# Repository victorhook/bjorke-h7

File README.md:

# 🛩️ Bjorke H7 Flight Controller

Bjorke H7 is a fully open source high-performance, ArduPilot-compatible flight controller built around the powerful STM32H743VIT6 MCU. Designed for flexibility and reliability, it supports a wide range of applications—from autonomous drones to experimental robotics.

---

## 🔧 Key Features

### ⚙️ Processing Power
- **MCU**: STM32H743VIT6 (480 MHz, 2MB Flash, 1MB RAM)

### 🧭 Sensors
- **IMU**: ICM-42688-P – ultra-low noise 6-axis motion tracking
- **Barometer**: BMP388 – high-accuracy altimeter for reliable altitude estimation

### 🔄 Interfaces & I/O
- **8x Motor Outputs** via 2x ESC 8-pin JST connectors
- **8x UARTs** for telemetry, GPS, companion computers, etc.
- **1x I²C** for external sensors or peripherals
- **3x Servo Outputs** + **1x dedicated GPIO**
- **1x RGB Status LED**
- **2x extra ADC Input Pins** for external sensors
- **1x CAN** (with onboard TJA1051TK/3 transceiver) – plug-and-play UAVCAN support

### 💾 Storage & Logging
- **MicroSD card slot** for robust onboard logging

### 🔌 Power Architecture
- **5V @ 3A** DC-DC
- **3.3V @ 3A** DC-DC

---

## ⚡ Designed for ArduPilot
Bjorke H7 runs **ArduPilot firmware** with support for:
- Real-time telemetry
- In-flight parameter updates
- MAVLink compatibility
- Full hardware-in-the-loop (HITL) testing
- CAN-based peripherals (UAVCAN GPS, ESCs, etc.)

---

## 🚧 Status
- [X] PCB rev.A designed and ordered
- [X] hwdef.dat
- [X] PCB rev.A hardware validated
- [X] Initial bring-up with ArduPilot firmware
- [X] Lua scripting verified
- [ ] First takeoff achieved
- [ ] 1 hour flight time achieved
- [ ] 5 hours flight time achieved
- [ ] 10 hours flight time achieved
- [ ] 25 hours flight time achieved
- [ ] 50 hours flight time achieved
- [ ] 100 hours flight time achieved

---

## 🧪 Ideal for:
- Custom drones (quads, hexas, octos)
- Research platforms
- Robotics
- Developers who need **max control and visibility**

## Flashing
With a fresh board we must flash the ardupilot bootloader. This requires us to put the mcu in DFU mode, which is done by holding down the boot button while powering on the board.

### Ardupilot + bootloader
1. Hold down boot button while powering on the board. If you're on linux you can use `dmesg -w` to monitor usb acitivty and you should get something like `Product: DFU in FS Mode` show up.
2. Open STM32CubeProgrammer and connect with USB
3. Open the file in `binaries/arducopter_with_bl.hex` and press flash
4. Powercycle the board and you should see `bjorke-BL` registers itself as USB device at first, then once it leaves bootloader you should get `bjorke` as USB device, and a serial port, eg `/dev/ttyACM0`

### Ardupilot application only
1. Using the `uploader.py` in AP repo
    ```
    python3 Tools/scripts/uploader.py build/bjorke/bin/arducopter.apj
    ```
2. Or, after built in repo: 
    ```
    ./waf copter --upload
    ```

### Ardupilot bootloader only
1. Put into DFU (same as above)
2. Flash bootloader using either STM32CubeProgrammer, or `dfu-util` with:
    ```
    dfu-util -a 0 --dfuse-address 0x08000000 -D binaries/AP_Bootloader.bin -R
    ```

### Building the code
Enter the ardupilot repository and run:

#### Bootloader
Either using:
```
./Tools/scripts/build_bootloaders.py bjorke
```
Creates binaries in `Tools/bootloaders/`:
- `Tools/bootloaders/bjorke_bl.bin`
- `Tools/bootloaders/bjorke_bl.hex`

Or, using:
```
./waf configure --board bjorke --bootloader
./waf clean
./waf bootloader
```

Bootloader binaries should be built to `build/bjorke/bin`
- AP_Bootloader.apj
- AP_Bootloader.bin
- AP_Bootloader.hex

#### Application
For the application build we first must have built bootloader with `./Tools/scripts/build_bootloaders.py`.
This is because AP tooling seems to expect a bootloader binary in `Tools/bootloaders/`.

```
./waf configure --board bjorke
./waf copter
```

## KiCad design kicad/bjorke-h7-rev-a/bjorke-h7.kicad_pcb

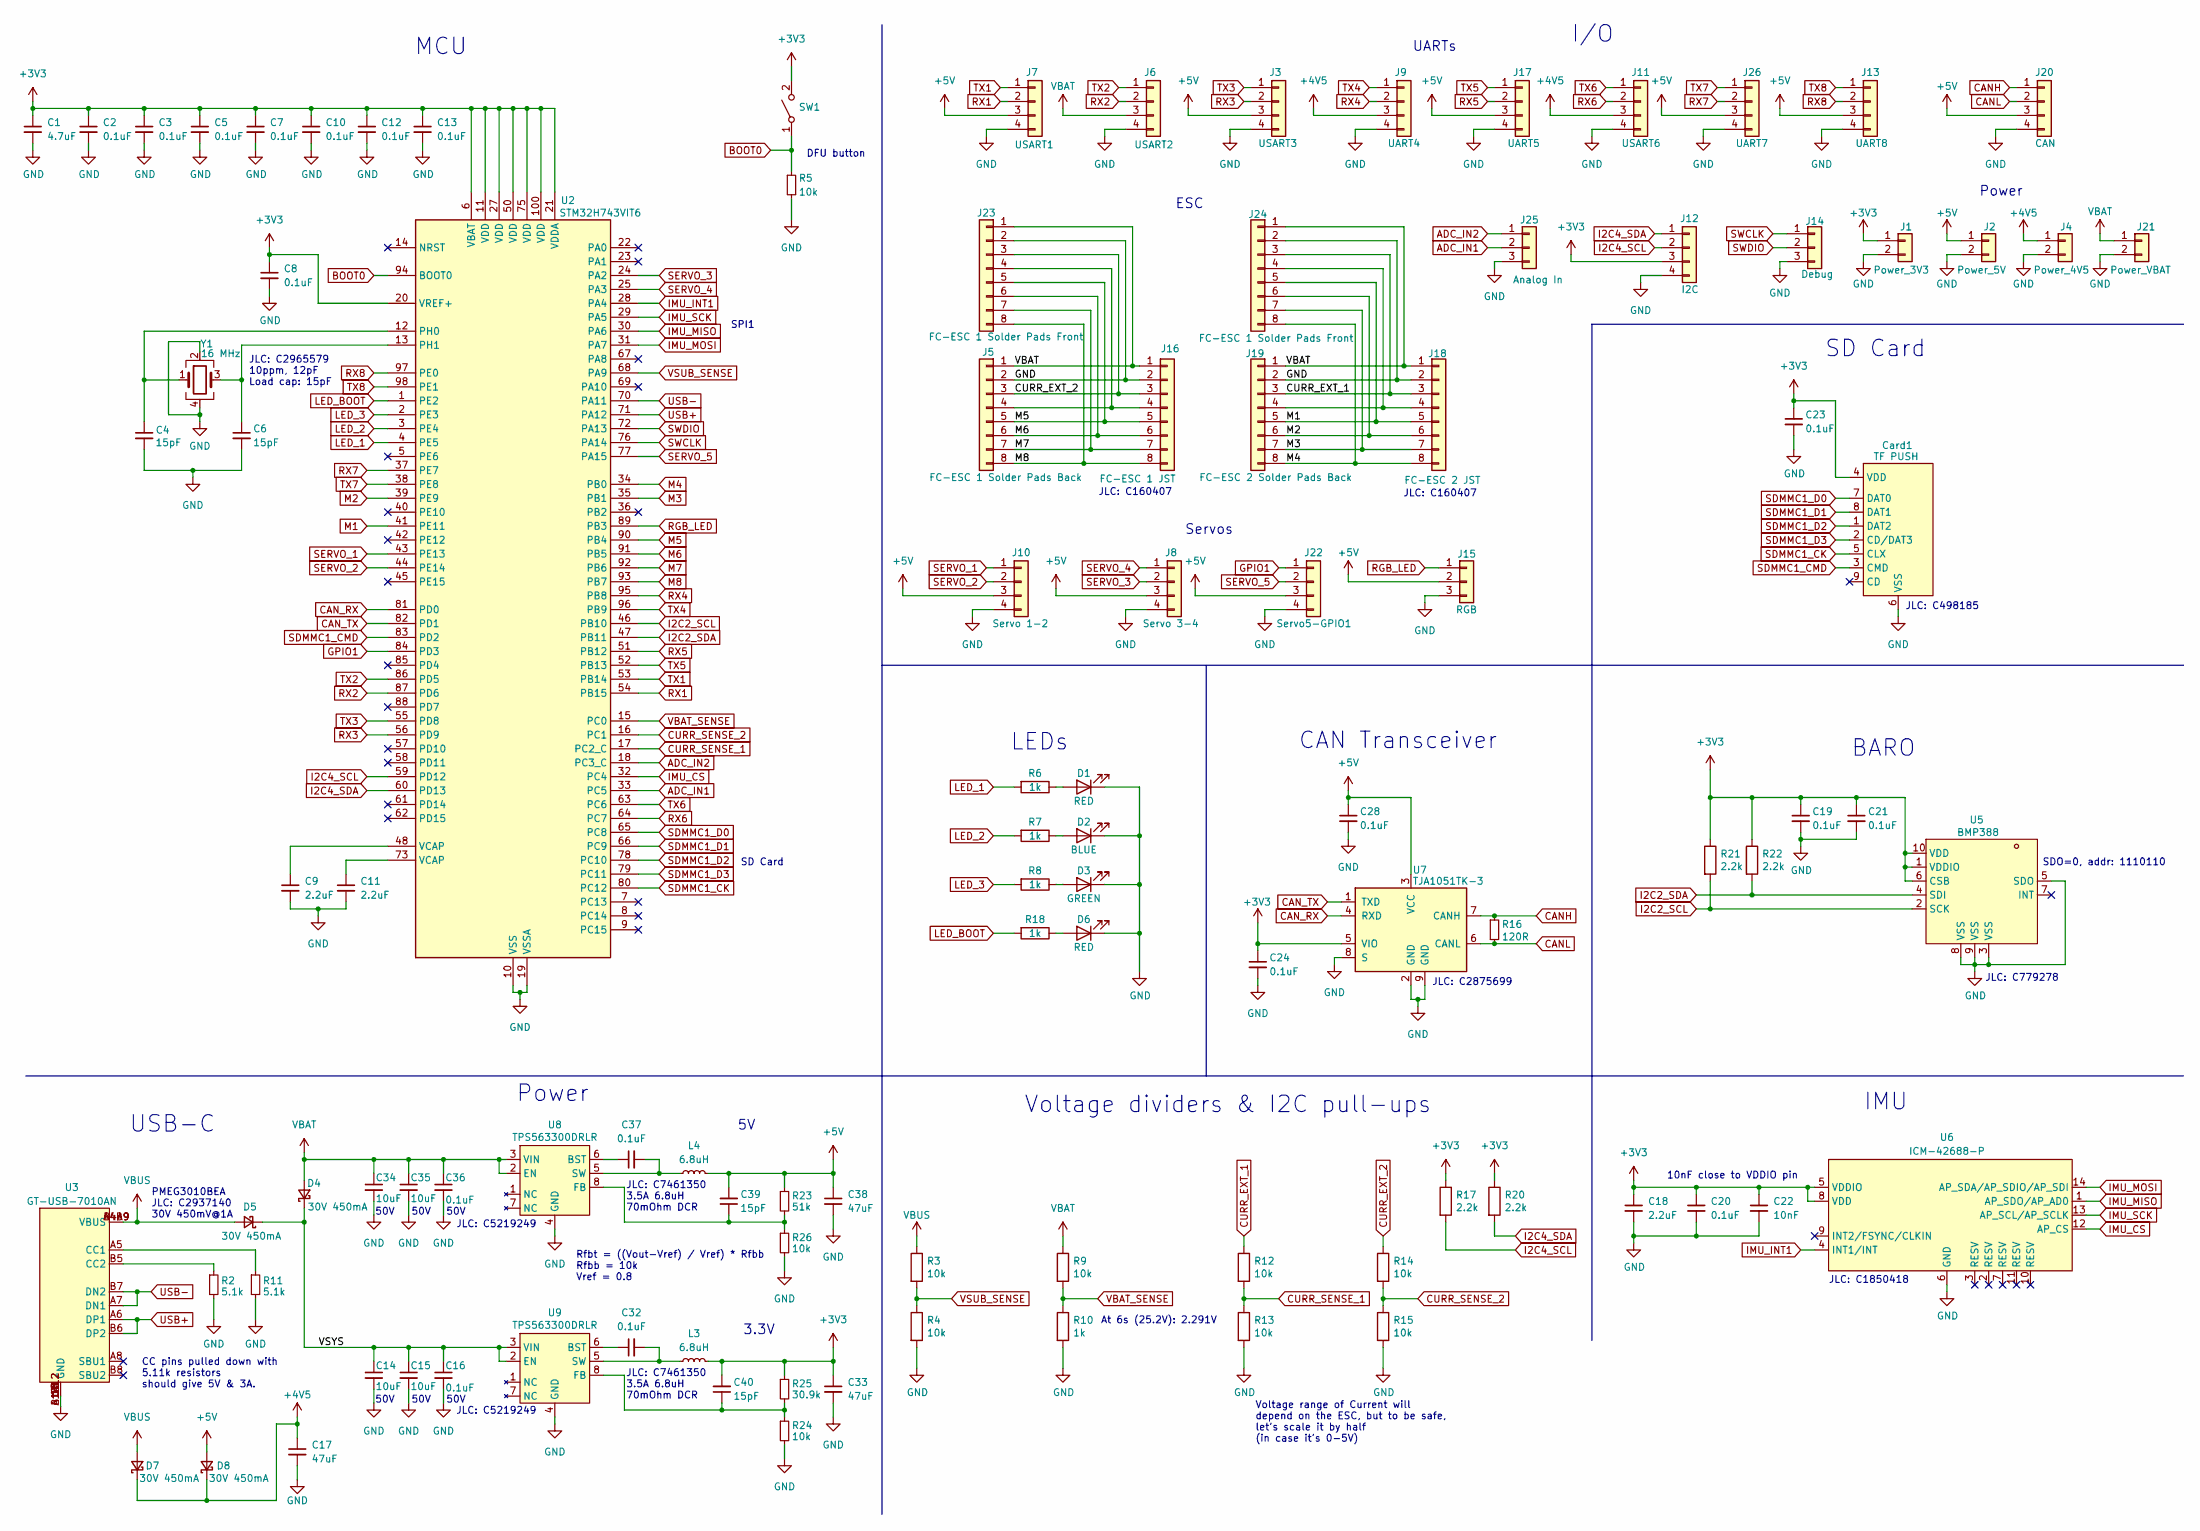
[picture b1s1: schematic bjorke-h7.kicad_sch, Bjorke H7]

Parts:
C1: 4.7uF; C_0402_1005Metric
C2, C3, C5, C7, C8, C10, C12, C13, C19, C20, C21, C23, C24, C28, C32, C37: 0.1uF; C_0402_1005Metric
C4, C6: 15pF; C_0402_1005Metric
C9, C11, C18: 2.2uF; C_0402_1005Metric
C14, C15, C34, C35: 10uF; C_0805_2012Metric; LCSC Part C440198
C16, C36: 0.1uF; C_0402_1005Metric; LCSC Part C307331
C17, C33, C38: 47uF; C_0805_2012Metric; LCSC Part C16780
C22: 10nF; C_0402_1005Metric
C39, C40: 15pF; C_0402_1005Metric; LCSC Part C1548
Card1: TF PUSH; TF-SMD_TF-021B-H265; LCSC Part C498185
D1, D6: RED; LED_0603_1608Metric
D2: BLUE; LED_0603_1608Metric
D3: GREEN; LED_0603_1608Metric
D4, D5, D7, D8: 30V 450mA; D_SOD-323; LCSC Part C2937140
J1: Power_3V3; Conn_2_Accesory_Bigger
J2: Power_5V; Conn_2_Accesory_Bigger
J3: USART3; Conn_4_Accesory_Bigger
J4: Power_4V5; Conn_2_Accesory_Bigger
J5: FC-ESC 1 Solder Pads Back; Conn_8_Accesory
J6: USART2; Conn_4_Accesory_Bigger_2x2
J7: USART1; Conn_4_Accesory_Bigger
J8: Servo 3-4; Conn_4_Accesory_Bigger
J9: UART4; Conn_4_Accesory_Bigger
J10: Servo 1-2; Conn_4_Accesory_Bigger
J11: USART6; Conn_4_Accesory_Bigger
J12: I2C; Conn_4_Accesory_Bigger
J13: UART8; Conn_4_Accesory_Bigger_2x2
J14: Debug; Conn_3_2.54_SMD
J15: RGB; Conn_3_Accesory_Bigger
J16: FC-ESC 1 JST; CONN-TH_SM08B-SRSS-TB-LF-SN
J17: UART5; Conn_4_Accesory_Bigger
J18: FC-ESC 2 JST; CONN-TH_SM08B-SRSS-TB-LF-SN
J19: FC-ESC 2 Solder Pads Back; Conn_8_Accesory
J20: CAN; Conn_4_Accesory_Bigger
J21: Power_VBAT; Conn_2_Accesory_Bigger
J22: Servo5-GPIO1; Conn_4_Accesory_Bigger
J23, J24: FC-ESC 1 Solder Pads Front; Conn_8_Accesory
J25: Analog In; Conn_3_Accesory_Bigger
J26: UART7; Conn_4_Accesory_Bigger
L3, L4: 6.8uH; IND-SMD_L5.7-W5.2; LCSC Part C7461350
R2, R11: 5.1k; R_0402_1005Metric
R3, R4, R5, R9, R12, R13, R14, R15: 10k; R_0402_1005Metric
R6, R7, R8, R10, R18: 1k; R_0402_1005Metric
R16: 120R; R_0402_1005Metric
R17, R20, R21, R22: 2.2k; R_0402_1005Metric
R23: 51k; R_0402_1005Metric; LCSC Part C25794
R24, R26: 10k; R_0402_1005Metric; LCSC Part C25744
R25: 30.9k; R_0402_1005Metric; LCSC Part C185428
SW1: SW_SPST; SW-SMD_TS-1086EV-16
U2: STM32H743VIT6; LQFP-100_14x14mm_P0.5mm
U3: GT-USB-7010AN; USB-SMD_GT-USB-7010AN; LCSC Part C963370
U5: BMP388; SENSORM-SMD_BMP388; LCSC Part C779278
U6: ICM-42688-P; LGA-14_L3.0-W2.5-P0.50-TL; LCSC Part C1850418
U7: TJA1051TK-3; HVSON-8-1EP_3x3mm_P0.65mm_EP1.6x2.4mm; LCSC Part C2875699
U8, U9: TPS563300DRLR; SOT-583-8_L2.1-W1.2-P0.50-LS1.6-BL; LCSC Part C5219249
Y1: 16 MHz; Crystal_SMD_2016-4Pin_2.0x1.6mm; LCSC Part C2965579

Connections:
+3V3: C1.1, C2.1, C3.1, C5.1, C7.1, C8.1, C10.1, C12.1, C13.1, C18.1, C19.1, C20.1, C21.1, C22.1, C23.1, C24.1, C33.1, C40.2, Card1.4 (VDD), J1.1, J12.3, L3.2, R17.1, R20.1, R21.1, R22.1, R25.1, SW1.2 (B), U2.6 (VBAT), U2.11 (VDD), U2.20 (VREF+), U2.21 (VDDA), U2.27 (VDD), U2.50 (VDD), U2.75 (VDD), U2.100 (VDD), U5.1 (VDDIO), U5.6 (CSB), U5.10 (VDD), U6.5 (VDDIO), U6.8 (VDD), U7.5 (VIO)
+4V5: C17.1, D7.1 (K), D8.1 (K), J4.1, J9.3, J11.3
+5V: C28.1, C38.1, C39.2, D8.2 (A), J2.1, J3.3, J7.3, J8.3, J10.3, J13.3, J15.2, J17.3, J20.3, J22.3, J26.3, L4.2, R23.1, U7.3 (VCC)
/VSYS: C14.1, C15.1, C16.1, D4.1 (K), D5.1 (K), U9.2 (EN), U9.3 (VIN)
ADC_IN1: J25.2, U2.33 (PC5)
ADC_IN2: J25.1, U2.18 (PC3_C)
BOOT0: R5.1, SW1.1 (A), U2.94 (BOOT0)
CANH: J20.1, R16.1, U7.7 (CANH)
CANL: J20.2, R16.2, U7.6 (CANL)
CAN_RX: U2.81 (PD0), U7.4 (RXD)
CAN_TX: U2.82 (PD1), U7.1 (TXD)
CURR_EXT_1: J18.3, J19.3, J24.3, R12.1
CURR_EXT_2: J5.3, J16.3, J23.3, R14.1
CURR_SENSE_1: R12.2, R13.1, U2.17 (PC2_C)
CURR_SENSE_2: R14.2, R15.1, U2.16 (PC1)
GND: C1.2, C2.2, C3.2, C4.2, C5.2, C6.2, C7.2, C8.2, C9.2, C10.2, C11.2, C12.2, C13.2, C14.2, C15.2, C16.2, C17.2, C18.2, C19.2, C20.2, C21.2, C22.2, C23.2, C24.2, C28.2, C33.2, C34.2, C35.2, C36.2, C38.2, Card1.6 (VSS), D1.1 (K), D2.1 (K), D3.1 (K), D6.1 (K), J1.2, J2.2, J3.4, J4.2, J5.2, J6.4, J7.4, J8.4, J9.4, J10.4, J11.4, J12.4, J13.4, J14.3, J15.3, J16.2, J17.4, J18.2, J19.2, J20.4, J21.2, J22.4, J23.2, J24.2, J25.3, J26.4, R2.2, R4.2, R5.2, R10.2, R11.2, R13.2, R15.2, R24.2, R26.2, U2.10 (VSS), U2.19 (VSSA), U2.26 (VSS), U2.49 (VSS), U2.74 (VSS), U2.99 (VSS), U3.13 (GND), U3.14 (GND), U3.15 (GND), U3.16 (GND), U3.A1B12 (GND), U3.B1A12 (GND), U5.3 (VSS), U5.5 (SDO), U5.8 (VSS), U5.9 (VSS), U6.6 (GND), U7.2 (GND), U7.8 (S), U7.9 (GND), U8.4 (GND), U9.4 (GND), Y1.2, Y1.4
GPIO1: J22.1, U2.84 (PD3)
I2C2_SCL: R21.2, U2.46 (PB10), U5.2 (SCK)
I2C2_SDA: R22.2, U2.47 (PB11), U5.4 (SDI)
I2C4_SCL: J12.2, R17.2, U2.59 (PD12)
I2C4_SDA: J12.1, R20.2, U2.60 (PD13)
IMU_CS: U2.32 (PC4), U6.12 (AP_CS)
IMU_INT1: U2.28 (PA4), U6.4 (INT1/INT)
IMU_MISO: U2.30 (PA6), U6.1 (AP_SDO/AP_AD0)
IMU_MOSI: U2.31 (PA7), U6.14 (AP_SDA/AP_SDIO/AP_SDI)
IMU_SCK: U2.29 (PA5), U6.13 (AP_SCL/AP_SCLK)
LED_1: R6.2, U2.4 (PE5)
LED_2: R7.2, U2.3 (PE4)
LED_3: R8.2, U2.2 (PE3)
LED_BOOT: R18.2, U2.1 (PE2)
M1: J18.5, J19.5, J24.5, U2.41 (PE11)
M2: J18.6, J19.6, J24.6, U2.39 (PE9)
M3: J18.7, J19.7, J24.7, U2.35 (PB1)
M4: J18.8, J19.8, J24.8, U2.34 (PB0)
M5: J5.5, J16.5, J23.5, U2.90 (PB4)
M6: J5.6, J16.6, J23.6, U2.91 (PB5)
M7: J5.7, J16.7, J23.7, U2.92 (PB6)
M8: J5.8, J16.8, J23.8, U2.93 (PB7)
unnamed: C9.1, U2.48 (VCAP)
unnamed: C11.1, U2.73 (VCAP)
unnamed: D1.2 (A), R6.1
unnamed: D2.2 (A), R7.1
unnamed: D3.2 (A), R8.1
unnamed: D6.2 (A), R18.1
unnamed: J5.4, J16.4, J23.4
unnamed: J18.4, J19.4, J24.4
unnamed: C4.1, U2.12 (PH0), Y1.1
unnamed: C6.1, U2.13 (PH1), Y1.3
unnamed: R11.1, U3.A5 (CC1)
unnamed: R2.1, U3.B5 (CC2)
unnamed: C37.1, U8.6 (BST)
unnamed: C39.1, R23.2, R26.1, U8.8 (FB)
unnamed: C37.2, L4.1, U8.5 (SW)
unnamed: C32.1, U9.6 (BST)
unnamed: C40.1, R24.1, R25.2, U9.8 (FB)
unnamed: C32.2, L3.1, U9.5 (SW)
RGB_LED: J15.1, U2.89 (PB3)
RX1: J7.2, U2.54 (PB15)
RX2: J6.2, U2.87 (PD6)
RX3: J3.2, U2.56 (PD9)
RX4: J9.2, U2.95 (PB8)
RX5: J17.2, U2.51 (PB12)
RX6: J11.2, U2.64 (PC7)
RX7: J26.2, U2.37 (PE7)
RX8: J13.2, U2.97 (PE0)
SDMMC1_CK: Card1.5 (CLX), U2.80 (PC12)
SDMMC1_CMD: Card1.3 (CMD), U2.83 (PD2)
SDMMC1_D0: Card1.7 (DAT0), U2.65 (PC8)
SDMMC1_D1: Card1.8 (DAT1), U2.66 (PC9)
SDMMC1_D2: Card1.1 (DAT2), U2.78 (PC10)
SDMMC1_D3: Card1.2 (CD/DAT3), U2.79 (PC11)
SERVO_1: J10.1, U2.43 (PE13)
SERVO_2: J10.2, U2.44 (PE14)
SERVO_3: J8.2, U2.24 (PA2)
SERVO_4: J8.1, U2.25 (PA3)
SERVO_5: J22.2, U2.77 (PA15)
SWCLK: J14.1, U2.76 (PA14)
SWDIO: J14.2, U2.72 (PA13)
TX1: J7.1, U2.53 (PB14)
TX2: J6.1, U2.86 (PD5)
TX3: J3.1, U2.55 (PD8)
TX4: J9.1, U2.96 (PB9)
TX5: J17.1, U2.52 (PB13)
TX6: J11.1, U2.63 (PC6)
TX7: J26.1, U2.38 (PE8)
TX8: J13.1, U2.98 (PE1)
USB+: U2.71 (PA12), U3.A6 (DP1), U3.B6 (DP2)
USB-: U2.70 (PA11), U3.A7 (DN1), U3.B7 (DN2)
VBAT: C34.1, C35.1, C36.1, D4.2 (A), J5.1, J6.3, J16.1, J18.1, J19.1, J21.1, J23.1, J24.1, R9.1, U8.2 (EN), U8.3 (VIN)
VBAT_SENSE: R9.2, R10.1, U2.15 (PC0)
VBUS: D5.2 (A), D7.2 (A), R3.1, U3.A4B9 (VBUS), U3.B4A9 (VBUS)
VSUB_SENSE: R3.2, R4.1, U2.68 (PA9)

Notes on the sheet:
JLC: C5219249
Voltage dividers & I2C pull-ups
JLC: C2965579 10ppm, 12pF Load cap: 15pF
At 6s (25.2V): 2.291V
50V
SD Card
I/O
JLC: C160407
JLC: C498185
Voltage range of Current will depend on the ESC, but to be safe, let's scale it by half (in case it's 0-5V)
LEDs
ESC
IMU
JLC: C1850418
JLC: C7461350 3.5A 6.8uH 70mOhm DCR
BARO
DFU button
UARTs
10nF close to VDDIO pin
JLC: C779278
JLC: C2875699
3.3V
SDO=0, addr: 1110110
CC pins pulled down with 5.11k resistors should give 5V & 3A.
USB-C
Power
Servos
PMEG3010BEA JLC: C2937140 30V 450mV@1A
SPI1
CAN Transceiver
Rfbt = ((Vout-Vref) / Vref) * Rfbb Rfbb = 10k Vref = 0.8
MCU

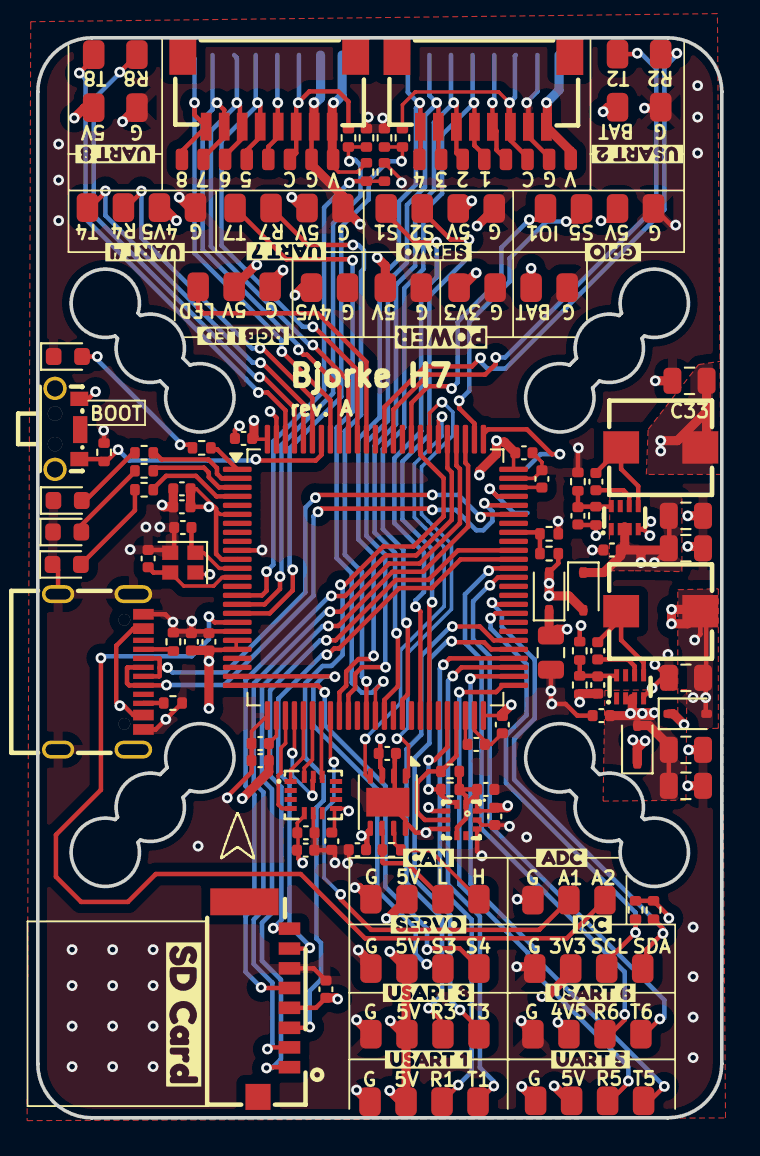
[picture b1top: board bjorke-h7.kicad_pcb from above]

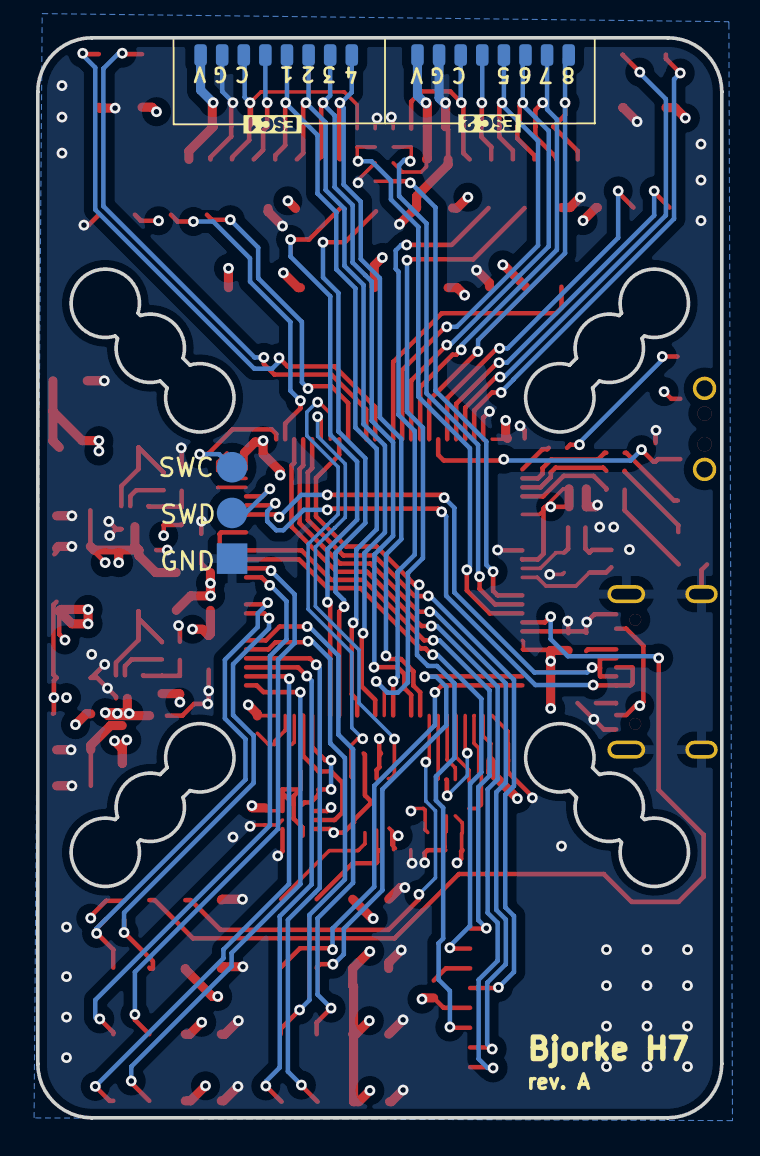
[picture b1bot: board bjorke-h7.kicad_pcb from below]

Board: 4 copper layers, 38.0 x 60.0 mm, 123 parts (5 on the bottom side), 92 nets.

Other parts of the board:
kibuzzard-67DE5AB0: G***; kibuzzard-67DE5AB0
kibuzzard-67DE5AD0: G***; kibuzzard-67DE5AD0
kibuzzard-67DE5AF3: G***; kibuzzard-67DE5AF3
kibuzzard-67DE5B23: G***; kibuzzard-67DE5B23
kibuzzard-67DE5B50: G***; kibuzzard-67DE5B50
kibuzzard-67DE5E84: G***; kibuzzard-67DE5E84
kibuzzard-67DE5E92: G***; kibuzzard-67DE5E92
kibuzzard-67DE57A5: G***; kibuzzard-67DE57A5
kibuzzard-67DE59DE: G***; kibuzzard-67DE59DE
kibuzzard-67DE573A: G***; kibuzzard-67DE573A
kibuzzard-67DE5740: G***; kibuzzard-67DE5740
kibuzzard-67DE5922: G***; kibuzzard-67DE5922
kibuzzard-67E2C95F: G***; kibuzzard-67E2C95F
kibuzzard-67EA1A9D: G***; kibuzzard-67EA1A9D
kibuzzard-67EA1ABB: G***; kibuzzard-67EA1ABB
kibuzzard-67EA1AD2: G***; kibuzzard-67EA1AD2
kibuzzard-67EA1AE5: G***; kibuzzard-67EA1AE5
kibuzzard-67EE0EFE: G***; kibuzzard-67EE0EFE
kibuzzard-67EE0F1B: G***; kibuzzard-67EE0F1B

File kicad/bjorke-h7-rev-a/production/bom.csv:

Designator,Footprint,Quantity,Value,LCSC Part #
C1,0402,1,4.7uF,
"C10, C12, C13, C19, C2, C20, C21, C23, C24, C28, C3, C32, C37, C5, C7, C8",0402,16,0.1uF,
"C11, C18, C9",0402,3,2.2uF,
"C14, C15, C34, C35",0805,4,10uF,C440198
"C16, C36",0402,2,0.1uF,C307331
"C17, C33, C38",0805,3,47uF,C16780
C22,0402,1,10nF,
"C39, C40",0402,2,15pF,C1548 
"C4, C6",0402,2,15pF,
Card1,TF-SMD_TF-021B-H265,1,TF PUSH,C498185
D1,0603,1,YELLOW,
D2,0603,1,BLUE,
D3,0603,1,GREEN,
"D4, D5, D7, D8",D_SOD-323,4,30V 450mA,C2762697
D6,0603,1,RED,
J1,Conn_2_Accesory_Bigger,1,Power_3V3,
J10,Conn_4_Accesory_Bigger,1,Servo 1-2,
J11,Conn_4_Accesory_Bigger,1,USART6,
J12,Conn_4_Accesory_Bigger,1,I2C,
J13,Conn_4_Accesory_Bigger_2x2,1,UART8,
J14,Conn_3_2.54_SMD,1,Debug,
J15,Conn_3_Accesory_Bigger,1,RGB,
J16,CONN-TH_SM08B-SRSS-TB-LF-SN,1,FC-ESC 1 JST,
J17,Conn_4_Accesory_Bigger,1,UART5,
J18,CONN-TH_SM08B-SRSS-TB-LF-SN,1,FC-ESC 2 JST,
J19,Conn_8_Accesory,1,FC-ESC 2 Solder Pads Back,
J2,Conn_2_Accesory_Bigger,1,Power_5V,
J20,Conn_4_Accesory_Bigger,1,CAN,
J21,Conn_2_Accesory_Bigger,1,Power_VBAT,
J22,Conn_4_Accesory_Bigger,1,Servo5-GPIO1,
"J23, J24",Conn_8_Accesory,2,FC-ESC 1 Solder Pads Front,
J25,Conn_3_Accesory_Bigger,1,Analog In,
J26,Conn_4_Accesory_Bigger,1,UART7,
J3,Conn_4_Accesory_Bigger,1,USART3,
J4,Conn_2_Accesory_Bigger,1,Power_4V5,
J5,Conn_8_Accesory,1,FC-ESC 1 Solder Pads Back,
J6,Conn_4_Accesory_Bigger_2x2,1,USART2,
J7,Conn_4_Accesory_Bigger,1,USART1,
J8,Conn_4_Accesory_Bigger,1,Servo 3-4,
J9,Conn_4_Accesory_Bigger,1,UART4,
"L3, L4",IND-SMD_L5.7-W5.2,2,6.8uH,C7461350
"R10, R18, R6, R7, R8",0402,5,1k,
"R11, R2",0402,2,5.1k,
"R12, R13, R14, R15, R3, R4, R5, R9",0402,8,10k,
R16,0402,1,120R,
"R17, R20, R21, R22",0402,4,2.2k,
R23,0402,1,51k,C25794
"R24, R26",0402,2,10k,C25744 
R25,0402,1,30.9k,C185428 
SW1,SW-SMD_TS-1086EV-16,1,SW_SPST,
U2,LQFP-100_14x14mm_P0.5mm,1,STM32H743VIT6,
U3,USB-SMD_GT-USB-7010AN,1,GT-USB-7010AN,C963370
U5,SENSORM-SMD_BMP388,1,BMP388,C779278
U6,LGA-14_L3.0-W2.5-P0.50-TL,1,ICM-42688-P,C1850418
U7,HVSON-8-1EP_3x3mm_P0.65mm_EP1.6x2.4mm,1,TJA1051TK-3,C2875699
"U8, U9",SOT-583-8_L2.1-W1.2-P0.50-LS1.6-BL,2,TPS563300DRLR,C5219249
Y1,Crystal_SMD_2016-4Pin_2.0x1.6mm,1,16 MHz,C2965579

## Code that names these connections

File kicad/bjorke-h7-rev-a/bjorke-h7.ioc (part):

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Mcu.Name=STM32H743VITx
Mcu.Package=LQFP100
Mcu.UserName=STM32H743VITx
PA11.Signal=USB_OTG_FS_DM
PA12.Signal=USB_OTG_FS_DP
PA13\ (JTMS/SWDIO).Signal=DEBUG_JTMS-SWDIO
PA14\ (JTCK/SWCLK).Signal=DEBUG_JTCK-SWCLK
PA15\ (JTDI).GPIOParameters=GPIO_Label
PA15\ (JTDI).GPIO_Label=SERVO5
PA15\ (JTDI).Signal=S_TIM2_CH1_ETR
PA2.GPIOParameters=GPIO_Label
PA2.GPIO_Label=SERVO3
PA2.Signal=S_TIM15_CH1
PA3.GPIOParameters=GPIO_Label
PA3.GPIO_Label=SERVO4
PA3.Signal=S_TIM15_CH2
PA4.GPIOParameters=GPIO_Label
PA4.GPIO_Label=IMU_INT
PA4.Signal=GPIO_Input
PA5.GPIOParameters=GPIO_Label
PA5.GPIO_Label=IMU_SCK
PA5.Signal=SPI1_SCK
PA6.GPIOParameters=GPIO_Label
PA6.GPIO_Label=IMU_MISO
PA6.Signal=SPI1_MISO
PA7.GPIOParameters=GPIO_Label
PA7.GPIO_Label=IMU_MOSI
PA7.Signal=SPI1_MOSI
PA9.Signal=USB_OTG_FS_VBUS
PB0.GPIOParameters=GPIO_Label
PB0.GPIO_Label=M4
PB0.Signal=S_TIM3_CH3
PB1.GPIOParameters=GPIO_Label
PB1.GPIO_Label=M3
PB1.Signal=S_TIM3_CH4
PB10.Signal=I2C2_SCL
PB11.Signal=I2C2_SDA
PB12.Signal=UART5_RX
PB13.Signal=UART5_TX
PB14.Signal=USART1_TX
PB15.Signal=USART1_RX
PB3\ (JTDO/TRACESWO).GPIOParameters=GPIO_Label
PB3\ (JTDO/TRACESWO).GPIO_Label=RGB_LED
PB3\ (JTDO/TRACESWO).Signal=S_TIM2_CH2
PB4\ (NJTRST).GPIOParameters=GPIO_Label
PB4\ (NJTRST).GPIO_Label=M5
PB4\ (NJTRST).Signal=S_TIM3_CH1
PB5.GPIOParameters=GPIO_Label
PB5.GPIO_Label=M6
PB5.Signal=S_TIM3_CH2
PB6.GPIOParameters=GPIO_Label
PB6.GPIO_Label=M7
PB6.Signal=S_TIM4_CH1
PB7.GPIOParameters=GPIO_Label
PB7.GPIO_Label=M8
PB7.Signal=S_TIM4_CH2
PB8.Signal=UART4_RX
PB9.Signal=UART4_TX
PC0.GPIOParameters=GPIO_Label
PC0.GPIO_Label=VBAT_SENSE
PC0.Signal=ADCx_INP10
PC1.GPIOParameters=GPIO_Label
PC1.GPIO_Label=CURRENT_SENSE_2
PC1.Signal=ADCx_INP11
PC10.Signal=SDMMC1_D2
PC11.Signal=SDMMC1_D3
PC12.Signal=SDMMC1_CK
PC2_C.GPIOParameters=GPIO_Label
PC2_C.GPIO_Label=CURRENT_SENSE_1
PC2_C.Mode=IN0-Single-Ended
PC2_C.Signal=ADC3_INP0
PC3_C.GPIOParameters=GPIO_Label
PC3_C.GPIO_Label=ADC_IN2
PC3_C.Signal=ADC3_INP1
PC4.GPIOParameters=GPIO_Label
PC4.GPIO_Label=IMU_CS
PC4.Signal=GPIO_Output
PC5.GPIOParameters=GPIO_Label
PC5.GPIO_Label=ADC_IN1
PC5.Signal=ADCx_INP8
PC6.Signal=USART6_TX
PC7.Signal=USART6_RX
PC8.Signal=SDMMC1_D0
PC9.Signal=SDMMC1_D1
PD0.Mode=FDCAN_Activate
PD0.Signal=FDCAN1_RX
PD1.Mode=FDCAN_Activate
PD1.Signal=FDCAN1_TX
PD12.Signal=I2C4_SCL
PD13.Signal=I2C4_SDA
PD2.Signal=SDMMC1_CMD
PD3.GPIOParameters=GPIO_Label
PD3.GPIO_Label=GPIO1
PD3.Signal=GPIO_Output
PD5.Signal=USART2_TX
PD6.Signal=USART2_RX
PD8.Signal=USART3_TX
PD9.Signal=USART3_RX
PE0.Signal=UART8_RX
PE1.Signal=UART8_TX
PE11.GPIOParameters=GPIO_Label
PE11.GPIO_Label=M1
PE11.Signal=S_TIM1_CH2
PE13.GPIOParameters=GPIO_Label
PE13.GPIO_Label=SERVO1
PE13.Signal=S_TIM1_CH3
PE14.GPIOParameters=GPIO_Label
PE14.GPIO_Label=SERVO2
PE14.Signal=S_TIM1_CH4
PE2.GPIOParameters=GPIO_Label
PE2.GPIO_Label=LED_BOOT
PE2.Signal=GPIO_Output
PE3.GPIOParameters=GPIO_Label
PE3.GPIO_Label=LED_3
PE3.Signal=GPIO_Output
PE4.GPIOParameters=GPIO_Label
PE4.GPIO_Label=LED_1
PE4.Signal=GPIO_Output
PE5.GPIOParameters=GPIO_Label
PE5.GPIO_Label=LED_2
PE5.Signal=GPIO_Output
PE7.Signal=UART7_RX
PE8.Signal=UART7_TX
PE9.GPIOParameters=GPIO_Label
PE9.GPIO_Label=M2
PE9.Signal=S_TIM1_CH1
PH0-OSC_IN\ (PH0).Mode=HSE-External-Oscillator
PH0-OSC_IN\ (PH0).Signal=RCC_OSC_IN
PH1-OSC_OUT\ (PH1).Mode=HSE-External-Oscillator
PH1-OSC_OUT\ (PH1).Signal=RCC_OSC_OUT
RCC.SYSCLKFreq_VALUE=64000000
board=custom

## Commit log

2025-04-11 Initial commit, rev.A ordered
2025-06-28 Updated README with build & flash instructions
2025-06-28 Added 3d model of pcb
2025-06-28 First working firmware!
    Built on `master` on AP, commit `aee973f4de9ce570d5302ab00cd72f2b8c6daece`.
2025-06-28 Added more bootloader info to readme
2025-06-28 AP 4.6.0 - v1.0
2025-07-15 Added upload scripts
